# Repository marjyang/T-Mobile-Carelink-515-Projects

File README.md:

# T-Mobile Carelink Projects

**Innovative IoT Healthcare Solutions - TECHIN 515 (Hardware Software Lab II)**

This repository contains three cutting-edge healthcare monitoring projects developed by GIX Cohort 8 as part of T-Mobile's remote healthcare data collection system initiative. Each project addresses critical healthcare challenges through IoT sensors, machine learning, and real-time data analytics.

## 🏥 Project Collection

### 1. **KneeHeal** - ACL Rehabilitation Monitoring
**📂 Branch: [`kneeheal-project`](https://github.com/marjyang/T-Mobile-Carelink-515-Projects/tree/kneeheal-project)**

Advanced ACL rehabilitation system using dual MPU6050 sensors and machine learning to track knee flexion angles during physical therapy exercises.

**Key Features:**
- Real-time knee angle monitoring with dual sensors
- Machine learning prediction model for accurate angle calculation
- React-based patient and doctor dashboards
- Firebase real-time data synchronization
- Progress tracking and exercise recommendations

**Technology Stack:** React.js, Firebase, Python ML, MPU6050 sensors, Arduino/ESP32

**Contributors:** Kelly Peng, Diana Ding, Yourong Xu, Jialu Huang

---

### 2. **Carelink Hypertension IoT Pill Box**
**📂 Branch: [`carelink-pillbox-project`](https://github.com/marjyang/T-Mobile-Carelink-515-Projects/tree/carelink-pillbox-project)**

Smart IoT-enabled pill tracking system for managing hypertension, combining sensor data and gesture detection to verify medication intake.

**Key Features:**
- Pill presence detection using photoresistor values
- ESP32-CAM captures image frames and sends them to a Flask server
- MediaPipe Pose runs on the server to detect pill-taking gestures
- Gesture signal is smoothed using a Savitzky–Golay low-pass filter to reduce noise
- Real-time data logging to Firebase Firestore for cloud storage
- React-based dashboard for patients and caregivers
- Notifications for missed doses and inconsistent behavior
- Designed for remote monitoring and healthcare provider integration

**Technology Stack:** React.js, Firebase, Flask, MediaPipe, Photoresistors, ESP32S3 Camera Module

**Contributors:** Yishuai Zheng, Hannah Xiao, Chang Li, Marjorie Yang

---

### 3. **X Heal** - ACL Rehabilitation Exercise Monitoring
**📂 Branch: [`Xheal-project`](https://github.com/marjyang/T-Mobile-Carelink-515-Projects/tree/Xheal-project)**

Intelligent ACL rehab tracker using TOF and SEN0221 sensors to detect and validate straight leg raise motions with real-time feedback and Firebase integration.

**Key features**
- Dual-sensor system using TOF (VL53L0X) for height and SEN0221 for angle
- Real-time motion tracking for straight leg raise
- Automatic repetition counting based on height thresholds and posture validity
- BLE data transmission from both sensors to React-based interface
- Firebase integration for cloud-based data storage and progress monitoring
- Patient-therapist dashboard with intuitive feedback
  
**Technology Stack:** React.js, Firebase (Firestore & Storage), ESP32-C3, ESP32-S3, VL53L0X (TOF), SEN0221, JavaScript, PDFMake, BLE

**Contributors:** Auria Zhang, Jazmyn Zhang, Yunqing Zhao, Shangming Zhuo

---

## 🚀 Live Demo

**Visit the integrated demo website:**  
**🔗 [https://adorable-brigadeiros-c2240e.netlify.app/](https://adorable-brigadeiros-c2240e.netlify.app/)**

Navigate between projects to replicate live demonstrations of each healthcare solution.

## 🛠️ Quick Start Guide

### For KneeHeal Project:
```bash
# Clone repository and switch to KneeHeal branch
git clone https://github.com/marjyang/T-Mobile-Carelink-515-Projects.git
cd T-Mobile-Carelink-515-Projects
git checkout kneeheal-project

# Install dependencies
npm install
pip install -r requirements.txt

# Start applications
npm start                          # React app (localhost:3000)
python firebase_read_predict.py    # ML prediction service
```

### For Carelink Pill Box:
```bash
# 1. Clone the repository and switch to the Pill Box branch
git clone https://github.com/marjyang/T-Mobile-Carelink-515-Projects.git
cd T-Mobile-Carelink-515-Projects
git checkout carelink-pillbox-project

# 2. Upload ESP32 code
# (Use Arduino IDE or PlatformIO to flash code in /esp32/ after editing Wi-Fi SSID and password)

# 3. Run the React frontend (patient/caregiver portal)
cd portal
npm install
npm start

# 4. Run the Flask server (gesture recognition)
cd ../flask_server
python flask_server.py
```

### For X Heal Project:
```bash
# Clone repository and navigate to Xheal branch
git clone https://github.com/marjyang/T-Mobile-Carelink-515-Projects.git
cd T-Mobile-Carelink-515-Projects
git checkout Xheal-project
cd patient-portal                   # or doctor-portal
npm install
npm start
```

## 📊 Project Overview

| Project | Technology | Status | Branch/Folder |
|---------|------------|--------|---------------|
| **KneeHeal** | React, Firebase, Python ML, MPU6050 | ✅ Complete | [`kneeheal-project`](https://github.com/marjyang/T-Mobile-Carelink-515-Projects/tree/kneeheal-project) |
| **Pill Box** | React, Firebase, Cloud Backend (Flask), OV2640, GL5528 or similar | ✅ Complete | [`Carelink_Pillbox`](https://github.com/marjyang/T-Mobile-Carelink-515-Projects/tree/carelink-pillbox-project) |
| **X Heal** | React, Firebase, Signal Processing, VL53L0X, SEN0221  | ✅ Complete | [`Xheal-project`](https://github.com/marjyang/T-Mobile-Carelink-515-Projects/tree/Xheal-project) |

## 🏗️ Repository Structure

```
T-Mobile-Carelink-515-Projects/
├── main branch (this README)
├── kneeheal-project branch/
│   ├── src/                     # React application
│   ├── firebase_read_predict.py # ML prediction service
│   ├── mpu_angle_model.pkl      # Trained ML model
│   ├── SETUP.md                 # Detailed setup guide
│   └── ...
├── carelink-pillbox-project branch/ 
│   └── cam-esp32s3/             # Camera ESP script
│   └── ldr-esp32s3/             # Photoresistors ESP script
│   └── server/                  # Flask server script
│   └── portal/                  # React application
│       └── src/
│       └── ...
│   └── ...
├── Xheal-project branch/
│   ├── Arduino-code/           # ESP32 firmware for angle and height sensors
│   ├── assets/                 # Device photos, schematics, and assembly diagrams
│   ├── doctor-portal/          # Doctor-facing React dashboard
│   ├── patient-portal/         # Patient-facing React dashboard
│   └── README.md               # Project README with setup, flow, and description
└── src/                        # Shared components
    └── ...

```

## 🎯 Project Goals

These projects advance T-Mobile's healthcare initiative by:

- **Improving Patient Outcomes**: Real-time monitoring and feedback systems
- **Enhancing Care Delivery**: Tools for healthcare providers to monitor patients remotely
- **Reducing Healthcare Costs**: Preventive care through continuous monitoring
- **Advancing IoT in Healthcare**: Practical applications of connected medical devices
- **Data-Driven Insights**: Machine learning for predictive healthcare analytics

## 🔬 Technical Innovation

### KneeHeal Innovations:
- **Dual Sensor Fusion**: Advanced MPU6050 sensor integration for accurate movement tracking
- **Real-time ML Predictions**: Edge computing for immediate feedback during exercises
- **Intuitive UI/UX**: Patient-friendly interfaces for rehabilitation guidance
- **Clinical Integration**: Healthcare provider dashboards for patient monitoring

### Carelink Pill Box Innovations:
- **Smart Dispensing**: Automated medication management with IoT sensors
- **Adherence Tracking**: Real-time monitoring of medication compliance
- **Alert Systems**: Multi-channel notifications for patients and caregivers

## 👥 Contributors & Teams

### KneeHeal Team
- **Kelly Peng** - Full-Stack Development &Machine Learning 
- **Diana Ding** - Enclosure Design & UI/UX Design 
- **Yourong Xu** -  System Architecture
- **Jialu Huang** -  Hardware Integration & Sensor Systems

### Carelink Pill Box Team
- **Yishuai Zheng** - UI/UX Design & IoT Development
- **Hannah Xiao** - Industrial Design & Software Development
- **Chang Li** - Design & Frontend Development
- **Marjorie Yang** - System Integration & Project Management

### X Heal Team
- **Auria Zhang** - Full-Stack Development & Project Management
- **Yunqing Zhao** - Software Development & System Integration
- **Jazmyn Zhang** - Hardware Integration (Heel Device) & UI/UX Design (Doctor Portal) 
- **Shangming Zhuo** - Hardware Integration (Knee Device)& UI/UX Design (Patient Portal) 

## 🎓 Academic & Industry Partnership

### Academic Institution
**Global Innovation Exchange (GIX) - University of Washington**
- **Course**: TECHIN 515 (Hardware Software Lab II)
- **Program**: Technology Innovation Master's Program
- **Cohort**: GIX Cohort 8

### Industry Partner
**T-Mobile**
- **Initiative**: Remote Healthcare Data Collection System
- **Focus**: Expanding healthcare accessibility through technology

### Project Advisors
- **Candice Boyd** - T-Mobile Healthcare Innovation
- **Justin Ho** - T-Mobile Technical Leadership
- **Quasheery Ahmed** - T-Mobile Project Management
- **John Raiti** - GIX Faculty Advisor
- **Luyao Niu** - GIX Technical Advisor

## 📈 Impact & Applications

### Healthcare Impact
- **Patient Engagement**: Interactive systems that motivate patient participation
- **Clinical Efficiency**: Streamlined monitoring reduces healthcare provider workload
- **Data Collection**: Rich datasets for healthcare research and improvement
- **Accessibility**: Remote monitoring solutions for underserved populations

### Technical Applications
- **IoT in Healthcare**: Practical implementations of connected medical devices
- **Edge Computing**: Real-time processing for immediate patient feedback
- **ML in Medicine**: Applied machine learning for predictive healthcare
- **User-Centered Design**: Healthcare interfaces designed for diverse user needs

## 🔗 External Resources

- **Live Demo**: [https://adorable-brigadeiros-c2240e.netlify.app/](https://adorable-brigadeiros-c2240e.netlify.app/)
- **GIX Program**: [University of Washington Global Innovation Exchange](https://gix.uw.edu/)
- **T-Mobile Healthcare**: [T-Mobile Health Solutions](https://www.t-mobile.com/)

## 📞 Contact & Support

### Project Inquiries
**Primary Contact**: marjyang@uw.edu  
**Repository Maintainer**: Marjorie Yang

### Technical Support
For technical issues or questions about specific projects:
1. Check the project-specific documentation in respective branches/folders
2. Review setup guides (`SETUP.md` files)
3. Contact project team members directly
4. Submit issues through GitHub Issues

### Collaboration Opportunities
We welcome collaboration from:
- Healthcare professionals interested in IoT applications
- Developers working on similar healthcare solutions
- Researchers in medical technology and patient monitoring
- Industry partners exploring connected health solutions

---

## 📄 License & Attribution

This project collection was developed as part of TECHIN 515 coursework at the Global Innovation Exchange (GIX), University of Washington, in partnership with T-Mobile.

**Academic Year**: 2024-2025  
**Course**: TECHIN 515 - Hardware Software Lab II  
**Institution**: Global Innovation Exchange (GIX)  
**Industry Partner**: T-Mobile

For detailed licensing information, see individual project folders.

---

**⭐ Star this repository if these healthcare IoT solutions inspire your work!**

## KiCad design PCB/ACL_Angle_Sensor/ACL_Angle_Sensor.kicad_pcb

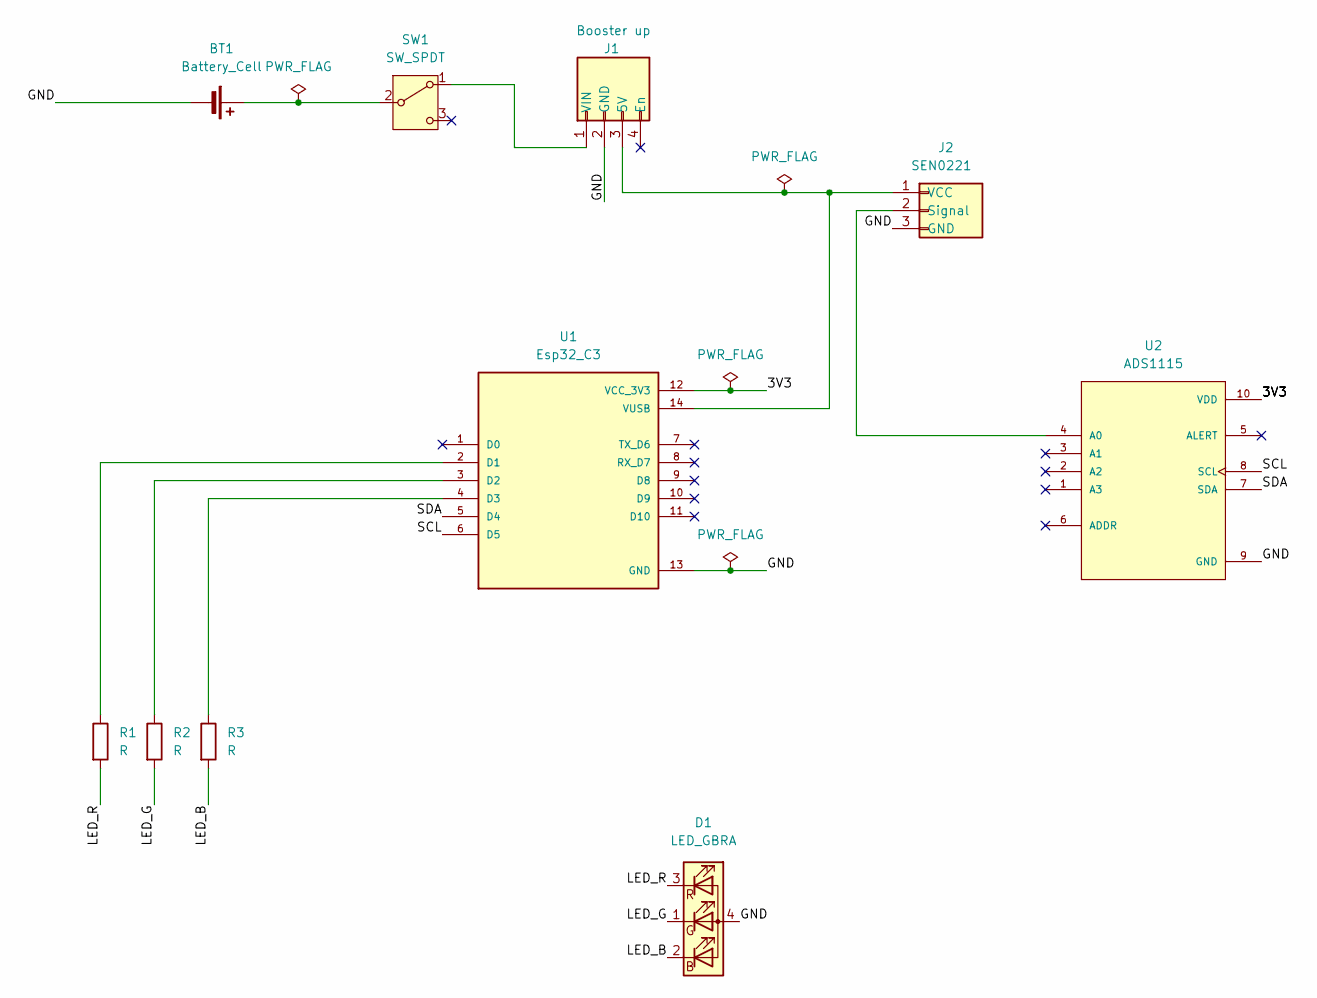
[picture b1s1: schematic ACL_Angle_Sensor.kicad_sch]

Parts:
BT1: Battery_Cell; JST_EH_B2B-EH-A_1x02_P2.50mm_Vertical
D1: LED_GBRA; LED_D5.0mm-4_RGB
J1: Booster up; PinSocket_1x04_P2.54mm_Vertical
J2: SEN0221; PinSocket_1x03_P2.54mm_Vertical
R1, R2, R3: R; R_0805_2012Metric
SW1: SW_SPDT; SW_MINI-SPDT-SW
U1: Esp32_C3; MODULE_113991054; PARTREV 23/05/2022
U2: ADS1115; MODULE_ZC261500; PARTREV NA

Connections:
/3V3: U1.12 (VCC_3V3), U2.10 (VDD)
/GND: BT1.2 (-), D1.4 (A), J1.2 (GND), J2.3 (GND), U1.13 (GND), U2.9 (GND)
/LED_B: D1.2 (BK), R3.2
/LED_G: D1.1 (GK), R2.2
/LED_R: D1.3 (RK), R1.2
/SCL: U1.6 (D5), U2.8 (SCL)
/SDA: U1.5 (D4), U2.7 (SDA)
unnamed: BT1.1 (+), SW1.2 (B)
unnamed: J1.3 (5V), J2.1 (VCC), U1.14 (VUSB)
unnamed: J1.1 (VIN), SW1.1 (A)
unnamed: J2.2 (Signal), U2.4 (A0)
unnamed: R1.1, U1.2 (D1)
unnamed: R2.1, U1.3 (D2)
unnamed: R3.1, U1.4 (D3)

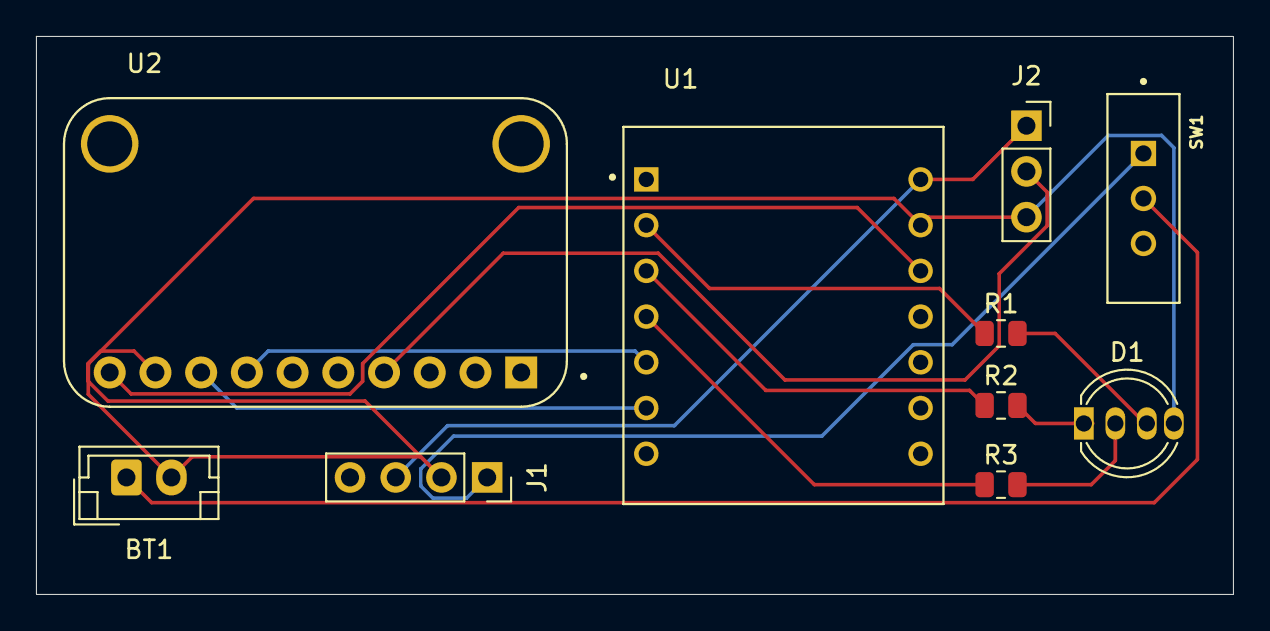
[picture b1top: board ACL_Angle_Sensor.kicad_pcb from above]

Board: 2 copper layers, 66.5 x 31.0 mm, 10 parts (0 on the bottom side), 14 nets.

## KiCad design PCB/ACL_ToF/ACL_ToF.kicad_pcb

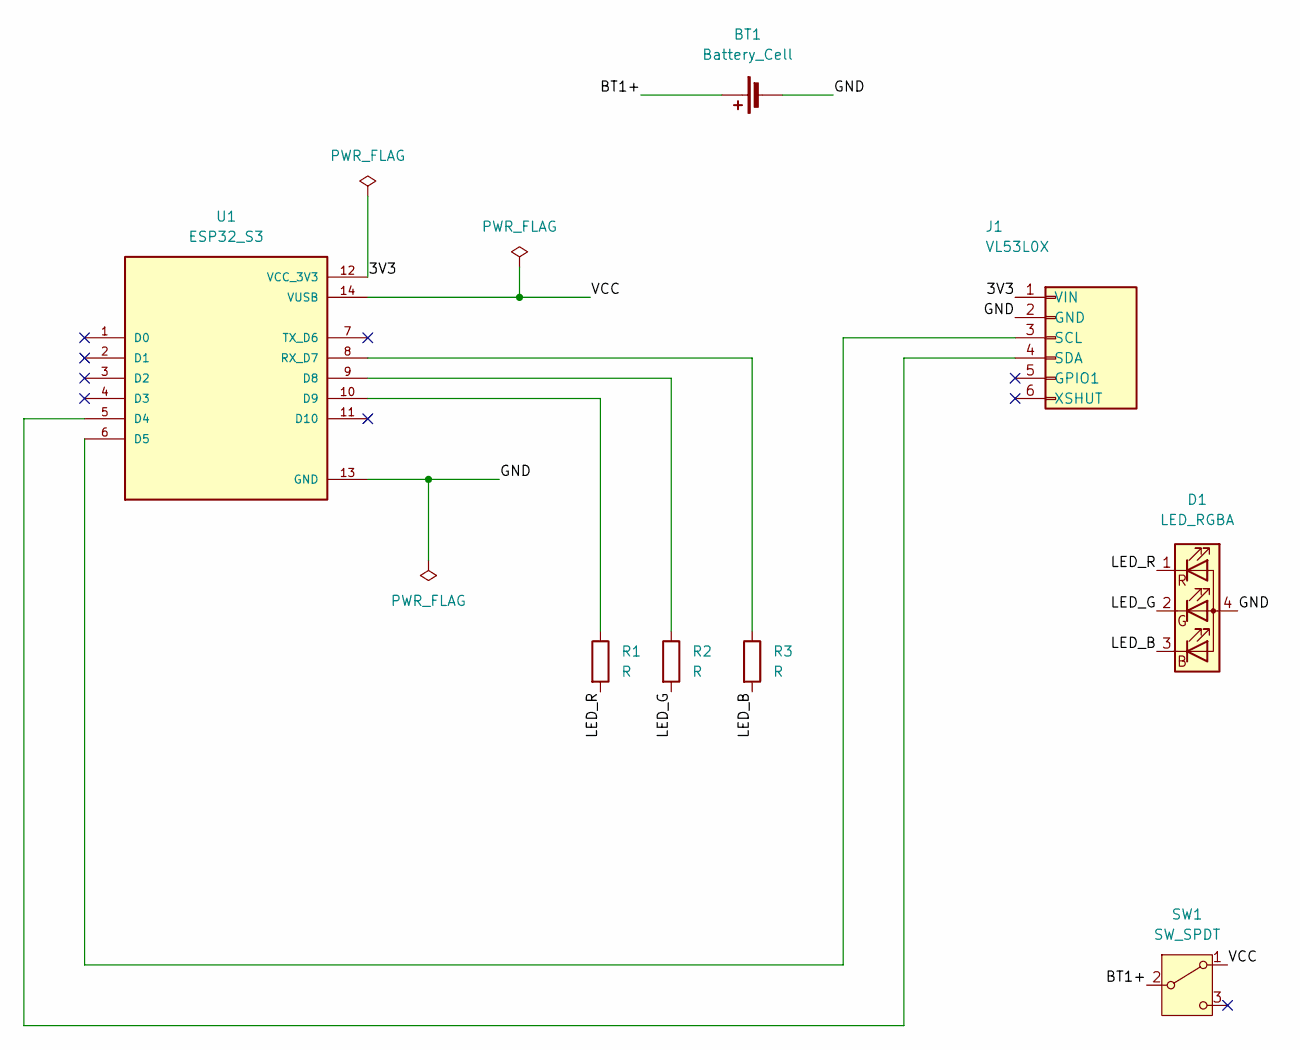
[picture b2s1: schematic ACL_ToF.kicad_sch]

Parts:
BT1: Battery_Cell; JST_PH_B2B-PH-K_1x02_P2.00mm_Vertical
D1: LED_RGBA; LED_D5.0mm-4_RGB
J1: VL53L0X; PinSocket_1x06_P2.54mm_Vertical
R1, R2, R3: R; R_0805_2012Metric
SW1: SW_SPDT; SW_MINI-SPDT-SW
U1: ESP32_S3; MODULE_113991054; PARTREV 23/05/2022

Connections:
/3V3: J1.1 (VIN), U1.12 (VCC_3V3)
/BT1+: BT1.1 (+), SW1.2 (B)
/GND: BT1.2 (-), D1.4 (A), J1.2 (GND), U1.13 (GND)
/LED_B: D1.3 (BK), R3.2
/LED_G: D1.2 (GK), R2.2
/LED_R: D1.1 (RK), R1.2
/VCC: SW1.1 (A), U1.14 (VUSB)
unnamed: J1.3 (SCL), U1.6 (D5)
unnamed: J1.4 (SDA), U1.5 (D4)
unnamed: R2.1, U1.9 (D8)
unnamed: R1.1, U1.10 (D9)
unnamed: R3.1, U1.8 (RX_D7)

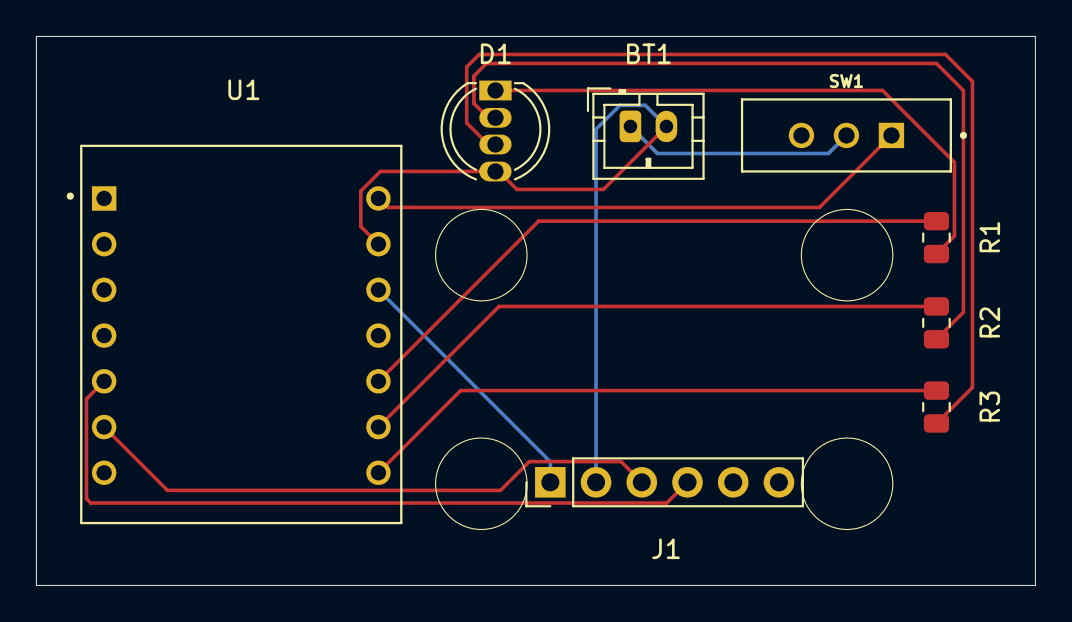
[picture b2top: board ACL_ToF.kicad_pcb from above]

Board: 2 copper layers, 55.5 x 30.5 mm, 8 parts (0 on the bottom side), 12 nets.

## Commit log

2025-05-12 Initialize project using Create React App
2025-06-06 ACL SRC
    ACL rehab team src
2025-06-06 Add KneeHeal ACL Rehabilitation Project - Complete React app with Firebase integration, ML prediction, dual MPU6050 sensors, real-time analytics. Contributors: Kelly Peng, Diana Ding, Yourong Xu, Jia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
2025-06-06 Update README.md to direct users to kneeheal-project branch - Added clear navigation instructions and branch structure information
2025-06-06 Create comprehensive main repository README for T-Mobile Carelink Projects collection
2025-06-06 Add comprehensive T-Mobile Carelink Projects main repository README - Professional overview of all healthcare IoT projects with clear navigation to KneeHeal branch
2025-06-09 edited medication tracking part
2025-06-09 carelink branch info update
2025-06-09 frontend part
2025-06-09 Update frontend setup instructions
2025-06-11 Create create Arduino_code folder
2025-06-13 Add enclosure files from TmobileCarelink repository
2025-06-13 docs: update README.md to focus on KneeHeal project only
2025-06-13 docs: add reference to SETUP.md in README
2025-06-13 docs: remove emojis from section titles in README
